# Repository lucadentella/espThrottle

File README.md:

# espThrottle

## Description

Portable device to control digital layouts using WiThrottle protocol.

## Features :trophy:

 - **TFT** color screen
 - **Battery** powered with built-in **USB charger**
 - Server **auto-discovery** (mDNS)
 - Configurable **favourite list** of locomotives
 - Support of JMRI **rosters**
 - Control of locomotive **speed** (128 steps) and **direction**
 - Control of 8 decoder **functions**
 - Layout **power** control
 - *Fixed address* mode

## Resources :open_file_folder:

 - [Eagle files](https://github.com/lucadentella/espThrottle/tree/main/Eagle) (schematic / PCB)
 - [Arduino firmware](https://github.com/lucadentella/espThrottle/tree/main/Arduino)
 - [3d printable case](https://github.com/lucadentella/espThrottle/tree/main/case) (STL)

## Documentation :notebook:

 - [User manual](https://github.com/lucadentella/espThrottle/tree/main/documentation/usermanual.md)
 - [Configuration manual](https://github.com/lucadentella/espThrottle/tree/main/documentation/configuration.md)
 - [How to use Roster Groups](https://github.com/lucadentella/espThrottle/tree/main/documentation/rostergroup.md)
 - [Part list](https://github.com/lucadentella/espThrottle/tree/main/documentation/partlist.md)

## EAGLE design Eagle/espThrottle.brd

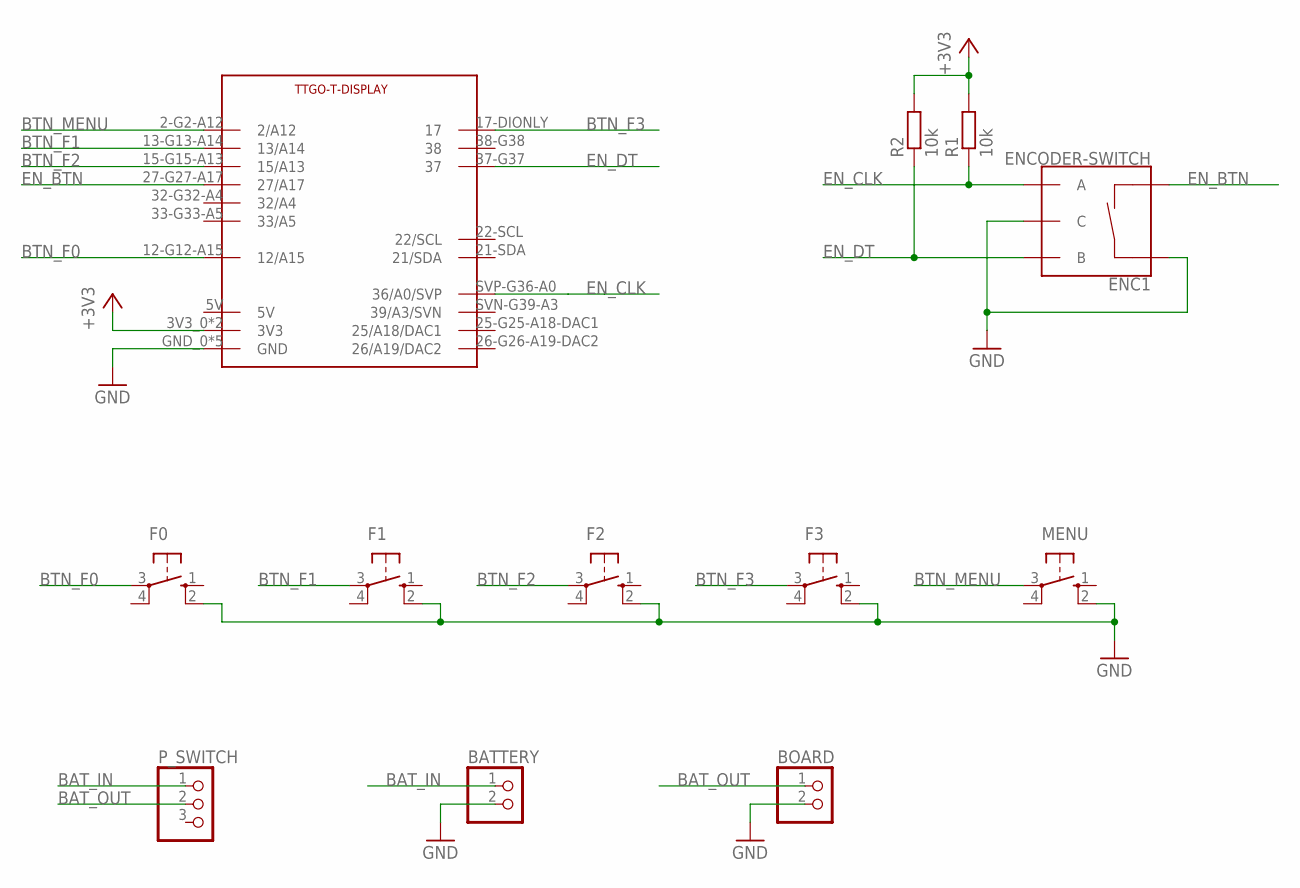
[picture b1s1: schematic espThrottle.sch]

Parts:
BATTERY: PINHD-1X2; 1X02
BOARD: PINHD-1X2; 1X02
ENC1: ENCODER-SWITCH; ROTARY_ENC_PLAIN
F0, F1, F2, F3: 10-XX; B3F-10XX
MENU: 10-XX; B3F-10XX
P_SWITCH: PINHD-1X3; 1X03
R1, R2: 10k; 0207/12
U$1: TTGO-T-DISPLAYFRAME; TTGO-T-DISPLAY-OL

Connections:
5V: U$1.5V
+3V3: R1.2, R2.2, U$1.3V3_0 (3V3), U$1.3V3_1 (3V3)
BAT_IN: BATTERY.1, P_SWITCH.1
BAT_OUT: BOARD.1, P_SWITCH.2
BTN_F0: F0.3, U$1.12-G12-A15 (12/A15)
BTN_F1: F1.3, U$1.13-G13-A14 (13/A14)
BTN_F2: F2.3, U$1.15-G15-A13 (15/A13)
BTN_F3: F3.3, U$1.17-DIONLY (17)
BTN_MENU: MENU.3, U$1.2-G2-A12 (2/A12)
EN_BTN: ENC1.SW-, U$1.27-G27-A17 (27/A17)
EN_CLK: ENC1.A, R1.1, U$1.SVP-G36-A0 (36/A0/SVP)
EN_DT: ENC1.B, R2.1, U$1.37-G37 (37)
GND: BATTERY.2, BOARD.2, ENC1.C, ENC1.SW+, F0.2 (S1), F1.2 (S1), F2.2 (S1), F3.2 (S1), MENU.2 (S1), U$1.GND_0 (GND), U$1.GND_1 (GND), U$1.GND_2 (GND), U$1.GND_3 (GND), U$1.GND_4 (GND)

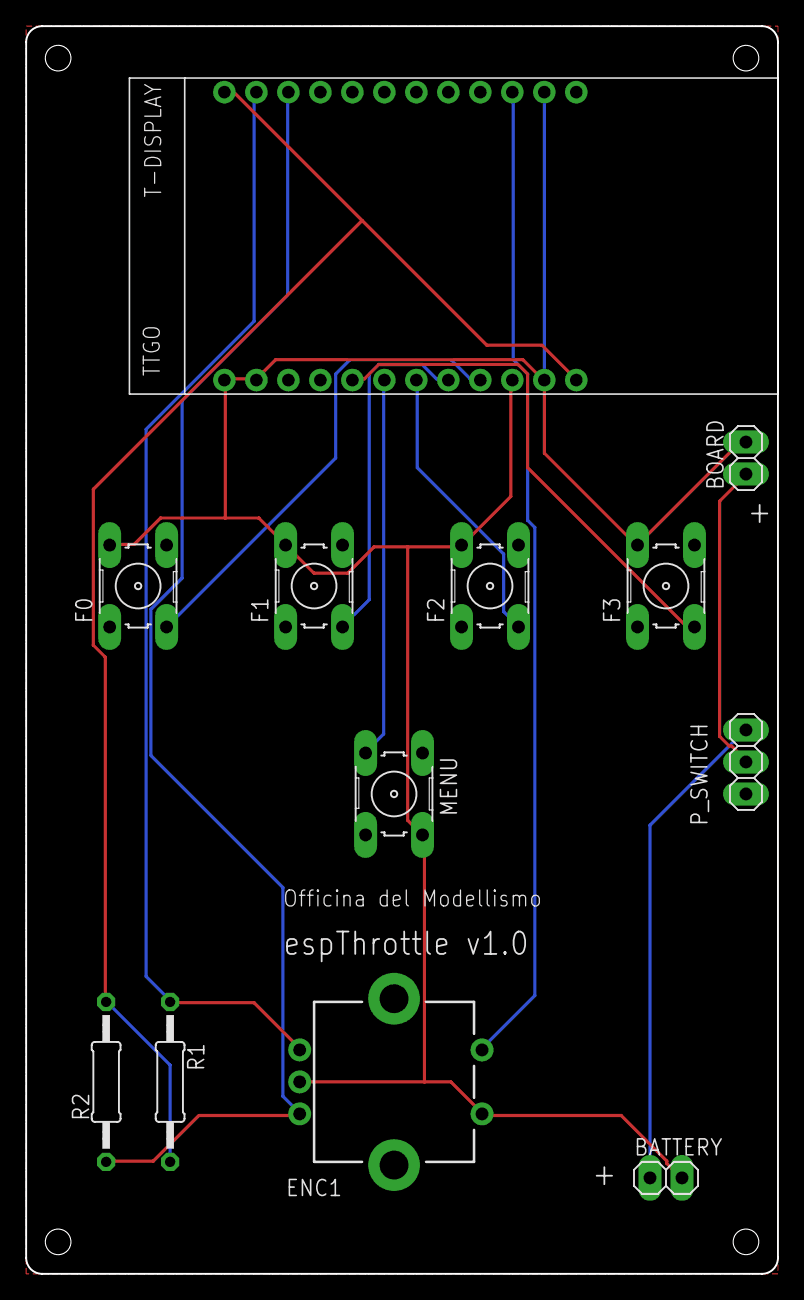
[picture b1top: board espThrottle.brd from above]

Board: 2 copper layers, 59.7 x 99.1 mm, 12 parts (0 on the bottom side), 12 nets.

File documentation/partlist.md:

# Part list
| ID | Description | 
|--|--|
| R1,R2 | Resistor, 10Kohm 1/4W |
| ENC1 | Rotary encoder |
| F0,F1,F2,F3,MENU | 6x6x15 momentary push buttons |
| TTGO | TTGO T-Display Development Board |
| PSWITCH| Angle slide switch |
| BAT | BL-5B battery |
| SCREWS | 4x 2mm self tapping screws |

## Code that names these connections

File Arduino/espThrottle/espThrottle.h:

#define VERSION "1.1"

// Loco struct
typedef struct {
  String locoName;
  int locoAddress;
  char locoAddressLength;
} loco;

#include <EEPROM.h>               // EEPROM to store parameters (server IP...)
#include <Adafruit_GFX.h>         // TFT display library (GFX + HAL + Font)
#include <Adafruit_ST7789.h>
#include <Fonts/FreeMono9pt7b.h>
#include <Fonts/FreeMono12pt7b.h>
#include <Fonts/FreeMonoBold12pt7b.h>
#include <Fonts/FreeMonoBold18pt7b.h>
#include <SPI.h>
#include <ESP32Encoder.h>         // Encoder library
#include <WiFi.h>                 // WiFi, mDNS and WiThrottle
#include <ESPmDNS.h>
#include <WiThrottle.h>
#include <esp_adc_cal.h>          // ADC calibration
#include "WiFiConnect.h"          // WiFi manager

#include "Config.h"
#include "Screens.h"
#include "RosterDelegate.h"
#include "Icons.h"

// Display
#define TFT_MOSI      19
#define TFT_SCLK      18
#define TFT_CS        5
#define TFT_RST       23
#define TFT_DC        16
#define TFT_BL        4
#define TFT_HEIGHT    135
#define TFT_WIDTH     240
#define TFT_ROTATION  3

// Encoder
#define ENCODER_A     36
#define ENCODER_B     37
#define ENCODER_BTN   27

// Buttons
#define BTN_F0        12
#define BTN_F1        13
#define BTN_F2        15
#define BTN_F3        17
#define BTN_MENU      2

// Battery monitor
#define BATTERY_PIN            34
#define BATTERY_CHECK_INTERVAL 2000

// EEPROM
#define EEPROM_SIZE   10

// Global objects
Adafruit_ST7789 tft = Adafruit_ST7789(TFT_CS, TFT_DC, TFT_MOSI, TFT_SCLK, TFT_RST);
ESP32Encoder encoder;
WiFiClient client;
WiThrottle wiThrottle;
RosterDelegate rosterDelegate;
WiFiConnect wc;

// Screens
Screen_Loco screenLoco;
Screen_Menu screenMenu;
Screen_ChangeAddr screenChangeAddr;
Screen_List screenList;
Screen_Server screenServer;
Screen* currentScreen;
bool redrawScreen;

// Screen positions
#define MENU_BOX_WIDTH          220
#define MENU_BOX_HEIGHT         120
#define ST77XX_GRAY             0xAD55

// Global variables
bool connected = false;

int vref = 1100;
int64_t encoderCount;
bool encoderBtnPressed;

int fBtns[4] = {BTN_F0, BTN_F1, BTN_F2, BTN_F3};
bool fBtnsPressed[4];
bool menuBtnPressed;
bool discardMenuBtn;

// Track info
TrackPower trackPower = PowerUnknown;

// Selected loco
int locoAddress = 1;
char locoAddressLength = 'S';
String locoName = "";
int locoSpeed;
Direction locoDirection;
bool locoFunctions[8];

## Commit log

2021-04-10 README updated
2021-04-11 Part list added
2021-04-16 Cover image added
2021-04-16 Configuration manual added
2021-04-16 Documentation about Roster Groups added
2021-04-16 User manual added
2021-04-16 Space between images fix
2021-04-16 Link to roster doc added

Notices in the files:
README.md:
License: CC-BY-NC-SA
parts and their libraries:
SparkFun-Switches: Licensing: Creative Commons ShareAlike 4.0 International - https://creativecommons.org/licenses/by-sa/4.0
